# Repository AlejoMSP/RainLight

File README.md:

# RainLight

Automotive rain light — 10-LED vertical array, KiCad project.

## Overview

10 red LEDs (D1–D10) in a vertical strip, each with its own current-limiting
resistor (R1–R10, 510Ω), powered from a 12V automotive source via a DTM04-2P
2-pin wire-pigtail connector (J1). Sized for a Chanzon 10mm red LED
(Vf ≈ 2.0V @ 20mA) running off battery/alternator voltage.

## Status

- **Schematic**: Rev 1.2, complete. See comments in the title block for revision
  history (LED polarity fix, per-LED resistor conversion, connector addition).
- **PCB**: in progress — footprint placement and routing underway.

## Key specs

| Item | Value |
|---|---|
| LEDs | D1–D10, red, THT 10mm (`LED_THT:LED_D10.0mm`) — Chanzon 10mm red, Vf ≈ 2.0V @ 20mA |
| Resistors | R1–R10, 510Ω, THT axial (`Resistor_THT:R_Axial_DIN0207_L6.3mm_D2.5mm_P7.62mm_Horizontal`) |
| Row spacing | ~16.4mm |
| Power input | J1, DTM04-2P wire pigtail, 2 pads (`Connector_Wire:SolderWire-0.75sqmm_1x02_P4.8mm_D1.25mm_OD2.3mm`) |
| Supply | 12V automotive |
| Per-LED current | ~19.6mA @ 12V nominal (R = (12V − 2V) / 20mA ≈ 500Ω, rounded to 510Ω) |

## Files

- `RainLight.kicad_pro` — project file
- `RainLight.kicad_sch` — schematic
- `RainLight.kicad_pcb` — PCB layout

`RainLight.kicad_prl` (local project settings) is gitignored — it's per-machine
session state, not meaningful to version.

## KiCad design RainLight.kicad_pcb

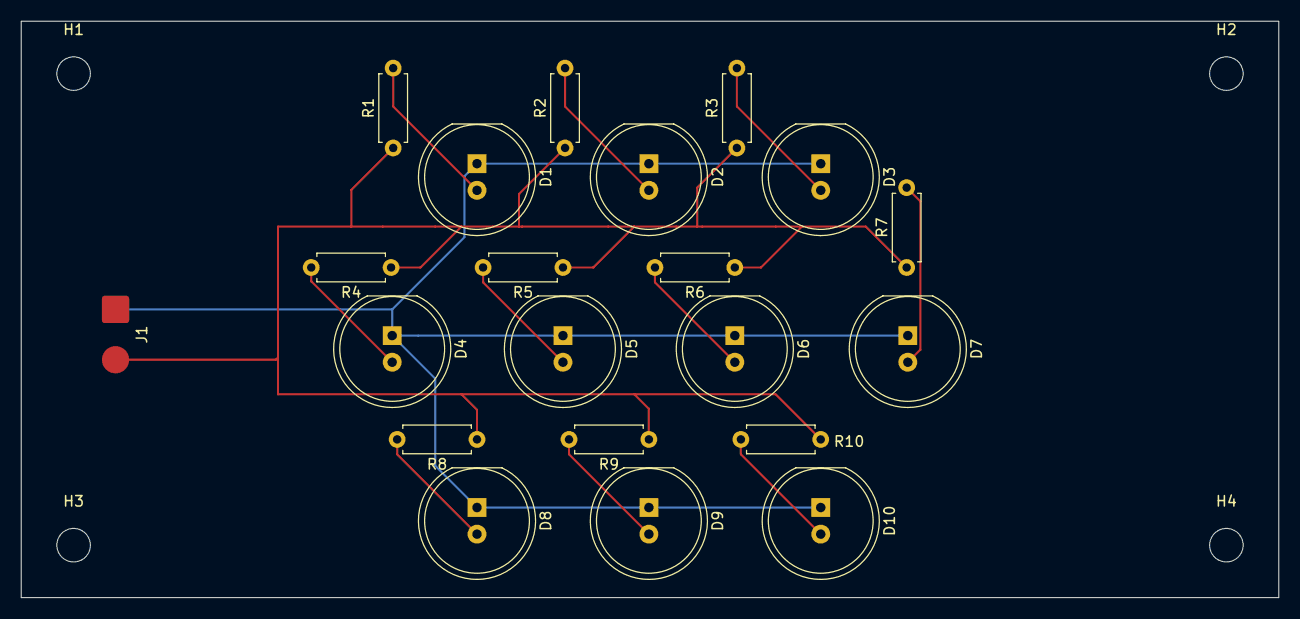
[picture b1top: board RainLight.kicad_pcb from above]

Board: 2 copper layers, 120.0 x 55.0 mm, 25 parts (0 on the bottom side), 12 nets.

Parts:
D1, D2, D3, D4, D5, D6, D7, D8, D9, D10: LED; LED_D10.0mm
H1, H2, H3, H4: MountingHole_3.2mm_M3
J1: DTM04-2P (wire pigtail); SolderWire-0.75sqmm_1x02_P4.8mm_D1.25mm_OD2.3mm
R1, R2, R3, R4, R5, R6, R7, R8, R9, R10: 510; R_Axial_DIN0207_L6.3mm_D2.5mm_P7.62mm_Horizontal

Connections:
GND: D1.1 (K), D2.1 (K), D3.1 (K), D4.1 (K), D5.1 (K), D6.1 (K), D7.1 (K), D8.1 (K), D9.1 (K), D10.1 (K), J1.1
unnamed: D1.2 (A), R1.2
unnamed: D2.2 (A), R2.2
unnamed: D3.2 (A), R3.2
unnamed: D4.2 (A), R4.2
unnamed: D5.2 (A), R5.2
unnamed: D6.2 (A), R6.2
unnamed: D7.2 (A), R7.2
unnamed: D8.2 (A), R8.2
unnamed: D9.2 (A), R9.2
unnamed: D10.2 (A), R10.2
VCC: J1.2, R1.1, R2.1, R3.1, R4.1, R5.1, R6.1, R7.1, R8.1, R9.1, R10.1
